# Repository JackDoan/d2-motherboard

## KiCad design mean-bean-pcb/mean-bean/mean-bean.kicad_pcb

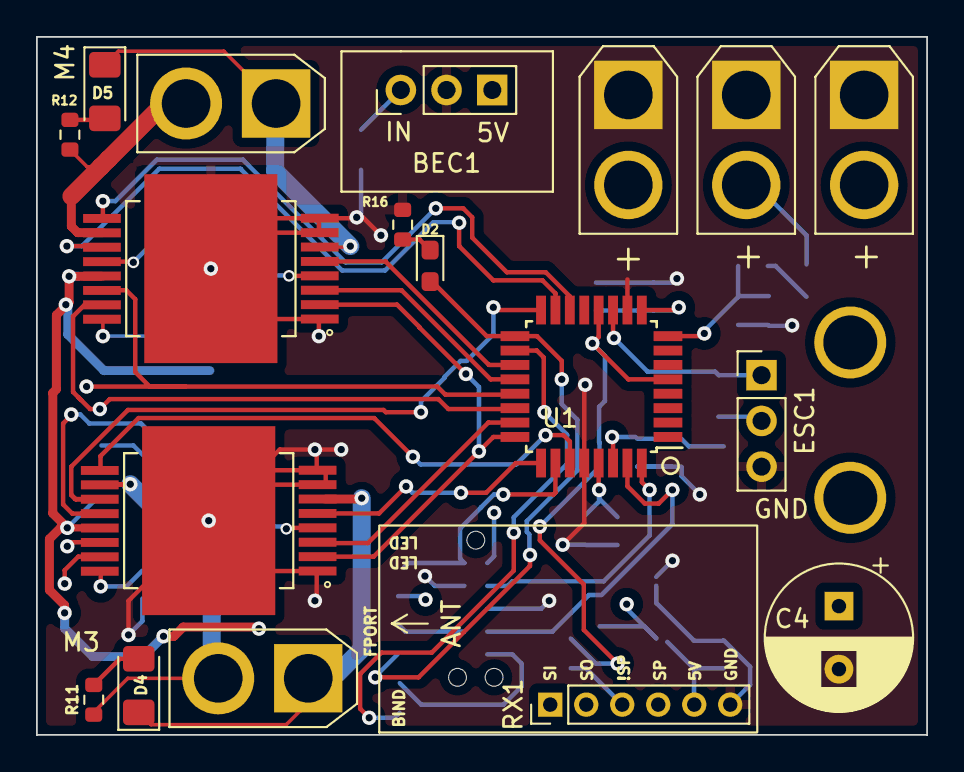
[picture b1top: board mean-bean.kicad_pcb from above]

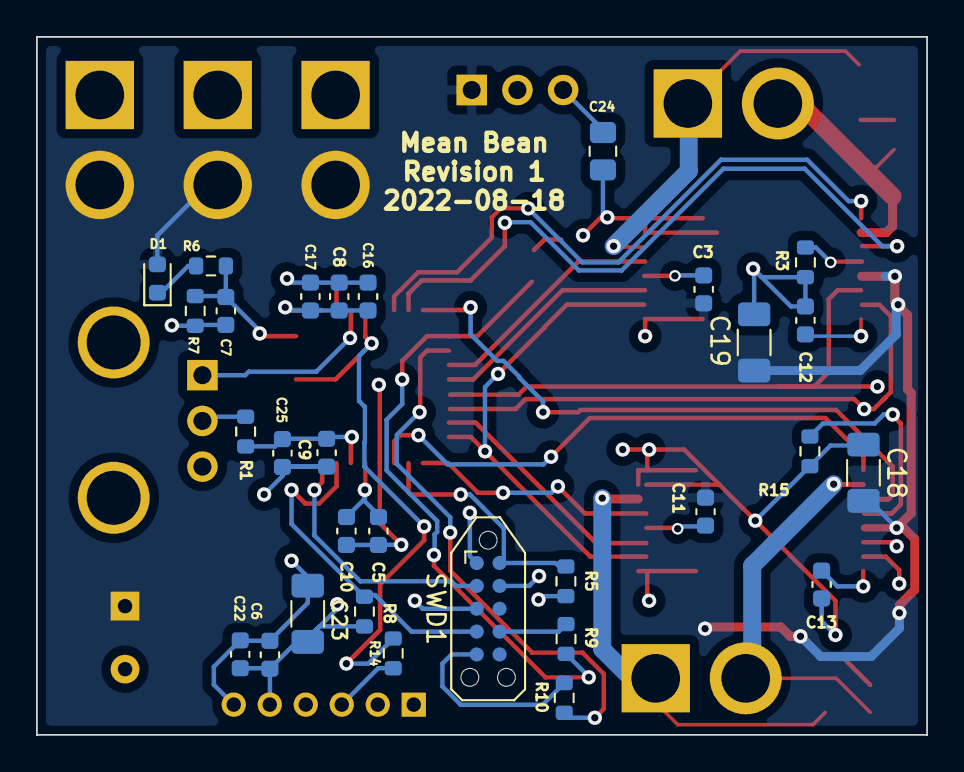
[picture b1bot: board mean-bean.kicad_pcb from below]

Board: 4 copper layers, 49.5 x 38.8 mm, 48 parts (30 on the bottom side), 39 nets.

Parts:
BATT1: Screw_Terminal_01x02; AMASS_XT30U-M_1x02_P5.0mm_Vertical
BEC1: BEC; PinHeader_1x03_P2.54mm_Vertical
C3, C5, C6, C7, C8, C11, C12, C13, C17: 0.1uF; C_0603_1608Metric
C4: 220uF; CP_Radial_D8.0mm_P3.50mm
C9, C16, C22, C25: 1uF; C_0603_1608Metric
C10: 1.0uF; C_0603_1608Metric
C18, C19, C23: 10uF; C_1206_3216Metric_Pad1.33x1.80mm_HandSolder
C24: 22uF; C_0805_2012Metric_Pad1.18x1.45mm_HandSolder
D1: D; D_0603_1608Metric
D2: LED; LED_0603_1608Metric_Pad1.05x0.95mm_HandSolder
D4, D5: LED_Dual_Bidirectional; LED_1206_3216Metric_Pad1.42x1.75mm_HandSolder
ESC1: BEC; PinHeader_1x03_P2.54mm_Vertical
J1, J2: Screw_Terminal_01x02; AMASS_XT30U-M_1x02_P5.0mm_Vertical
M3, M4: Screw_Terminal_01x02; AMASS_XT30U-F_1x02_P5.0mm_Vertical
R1: 0; R_0603_1608Metric
R3, R5, R6, R7, R15: 10k 1%; R_0603_1608Metric
R8: 1k 1%; R_0603_1608Metric
R9, R10: 10k; R_0603_1608Metric
R11, R12: 1.6k 1%; R_0603_1608Metric
R14: ?k 1%; R_0603_1608Metric
R16: 330; R_0603_1608Metric
RX1: RX; PinHeader_1x06_P2.00mm_Vertical
SWD1: Connector:Tag-Connect_TC2050-IDC-NL_2x05_P1.27mm_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; Tag-Connect_TC2050-IDC-NL_2x05_P1.27mm_Vertical
U1: PIC32CM6408MC00032-I/PT; TQFP-32_7x7mm_P0.8mm
U4, U5: L9958; IC_VND5T016ASPTR-E_wider_pads_scooted_0.05

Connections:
5V: BEC1.3, C6.2, C8.1, C9.1, C12.1, C13.1, C16.2, C17.2, C22.2, C23.2, C24.1, C25.1, R1.2, R5.2, R8.1, RX1.5, SWD1.1, U1.9 (VDDANA), U1.30 (VDDIN), U4.16 (VDD), U5.16 (VDD)
/Channel3/ChargePump: C11.1, U4.4 (CP)
/Channel3/RefCurrent: R15.1, U4.12 (REXT)
/Channel4/ChargePump: C3.1, U5.4 (CP)
/Channel4/RefCurrent: R3.1, U5.12 (REXT)
/VCORE: C5.1, C10.1, U1.29 (VDDCORE)
BATT: BATT1.2, BEC1.1, C3.2, C4.1, C11.2, C18.2, C19.2, D1.2 (A), J1.2, J2.2, U4.13 (VS), U5.13 (VS)
CS3: U1.23 (PA24), U4.3 (CS)
CS4: U1.20 (PA19), U5.3 (CS)
DIR3: U1.25 (PA27), U4.5 (DIR)
DIR4: U1.19 (PA18), U5.5 (DIR)
DSHOT_SERCOM2: ESC1.1, U1.11 (PA08)
EN3: U1.27 (PA28), U4.9 (EN)
EN4: U1.14 (PA11), U5.9 (EN)
FTDI_RXI: D2.2 (A), R9.1, U1.17 (PA16)
FTDI_RXI_CONN: R9.2, SWD1.7
FTDI_TXO: R10.1, U1.18 (PA17)
FTDI_TXO_CONN: R10.2, SWD1.5
GND: BATT1.1, BEC1.2, C4.2, C5.2, C6.1, C7.2, C8.2, C9.2, C10.2, C12.2, C13.2, C16.1, C17.1, C18.1, C19.1, C22.1, C23.1, C24.2, C25.2, ESC1.3, J1.1, J2.1, R3.2, R7.2, R15.2, R16.1, RX1.6, SWD1.3, SWD1.9, U1.10 (GNDANA), U1.28 (GND), U4.1 (GND), U4.7 (DI), U4.8 (PGND), U4.17 (Pad), U5.1 (GND), U5.7 (DI), U5.8 (PGND), U5.17 (Pad)
MISO: U1.24 (PA25), U4.2 (SO), U5.2 (SO)
MOSI: U1.21 (PA22), U4.14 (SI), U5.14 (SI)
unnamed: D1.1 (K), R6.1
unnamed: D2.1 (K), R16.2
unnamed: D4.2 (AK), R11.1
unnamed: D5.2 (AK), R12.1
unnamed: ESC1.2, R1.1
unnamed: R14.2, RX1.3
OUT3_N: M3.2, R11.2, U4.10 (OUT2)
OUT3_P: D4.1 (KA), M3.1, U4.6 (OUT1)
OUT4_N: M4.2, R12.2, U5.10 (OUT2)
OUT4_P: D5.1 (KA), M4.1, U5.6 (OUT1)
PWM3: U1.16 (PA15/XOUT), U4.11 (PWM)
PWM4: U1.15 (PA14/XIN), U5.11 (PWM)
RESET: R5.1, SWD1.10, U1.26 (RESET)
RX_FPORT_RX_SERCOM0: R14.1, U1.5 (PA04), U1.12 (PA09)
SCK: U1.22 (PA23), U4.15 (SCK), U5.15 (SCK)
SWCLK: R8.2, SWD1.4, U1.31 (PA30/SWCLK)
SWDIO: SWD1.2, U1.32 (PA31/SWDIO)
V_BATT_SENSE: C7.1, R6.2, R7.1, U1.8 (PA07)

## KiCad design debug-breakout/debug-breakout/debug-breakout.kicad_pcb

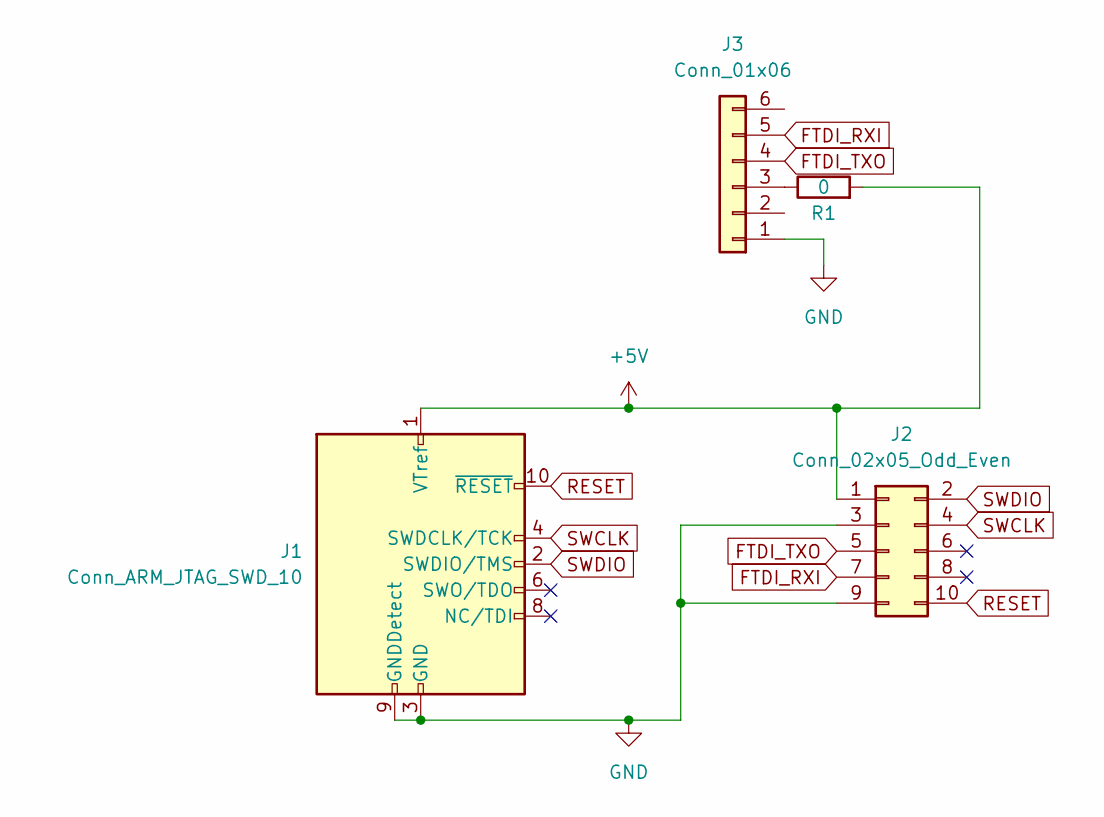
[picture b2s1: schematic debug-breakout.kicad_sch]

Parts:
J1: Conn_ARM_JTAG_SWD_10; PinHeader_2x05_P1.27mm_Vertical
J2: Conn_02x05_Odd_Even; PinHeader_2x05_P2.54mm_Vertical
J3: Conn_01x06; PinHeader_1x06_P2.54mm_Vertical
R1: 0; R_0603_1608Metric_Pad0.98x0.95mm_HandSolder

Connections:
+5V: J1.1 (VTref), J2.1, R1.2
FTDI_RXI: J2.7, J3.5
FTDI_TXO: J2.5, J3.4
GND: J1.3 (GND), J1.5 (GND), J1.9 (GNDDetect), J2.3, J2.9, J3.1
unnamed: J3.3, R1.1
RESET: J1.10 (~RESET), J2.10
SWCLK: J1.4 (SWDCLK/TCK), J2.4
SWDIO: J1.2 (SWDIO/TMS), J2.2

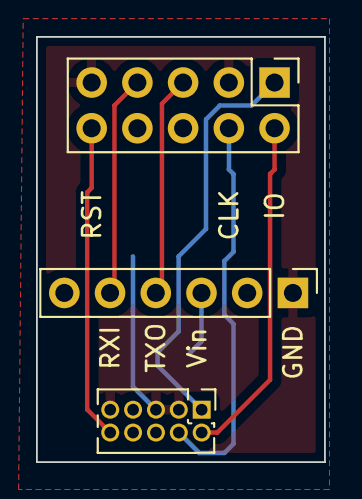
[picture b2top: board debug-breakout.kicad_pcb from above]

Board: 2 copper layers, 16.0 x 23.6 mm, 4 parts (1 on the bottom side), 8 nets.

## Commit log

2022-08-17 add debug board
2022-08-18 rev2
2022-09-04 mean bean
